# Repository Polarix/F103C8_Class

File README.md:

# STM32F103C8单片机核心板
这是一款设计用于STM32F103C8T6单片机及引脚布局兼容单片机的核心板设计。

原理图和PCB设计使用KiCAD完成，依赖以下符号库和封装库。
 - [kicad_libs_append](https://github.com/Polarix/kicad_libs_append)

## 设计目标
电路设计尝试兼容以下芯片及其引脚兼容型号：

|型号|封装|特征及其改动|
|-|-|-|
|STM32F103C8T6|LQFP-48|以此为基础型号。|
|STM32F030C8T6|LQFP-48|取消一组电源，35、36两个引脚增加PF6、PF7两个GPIO，可复用为USART3的TX、RX两个引脚以及TIM16和TIM17的1通道。|
|STM32F401CCU6|QFN-48|34脚改为VCAP，用作内部电压调节器滤波，并取消了PB11引脚，USART3不可用并被替换为了USART6。|

## 预览图

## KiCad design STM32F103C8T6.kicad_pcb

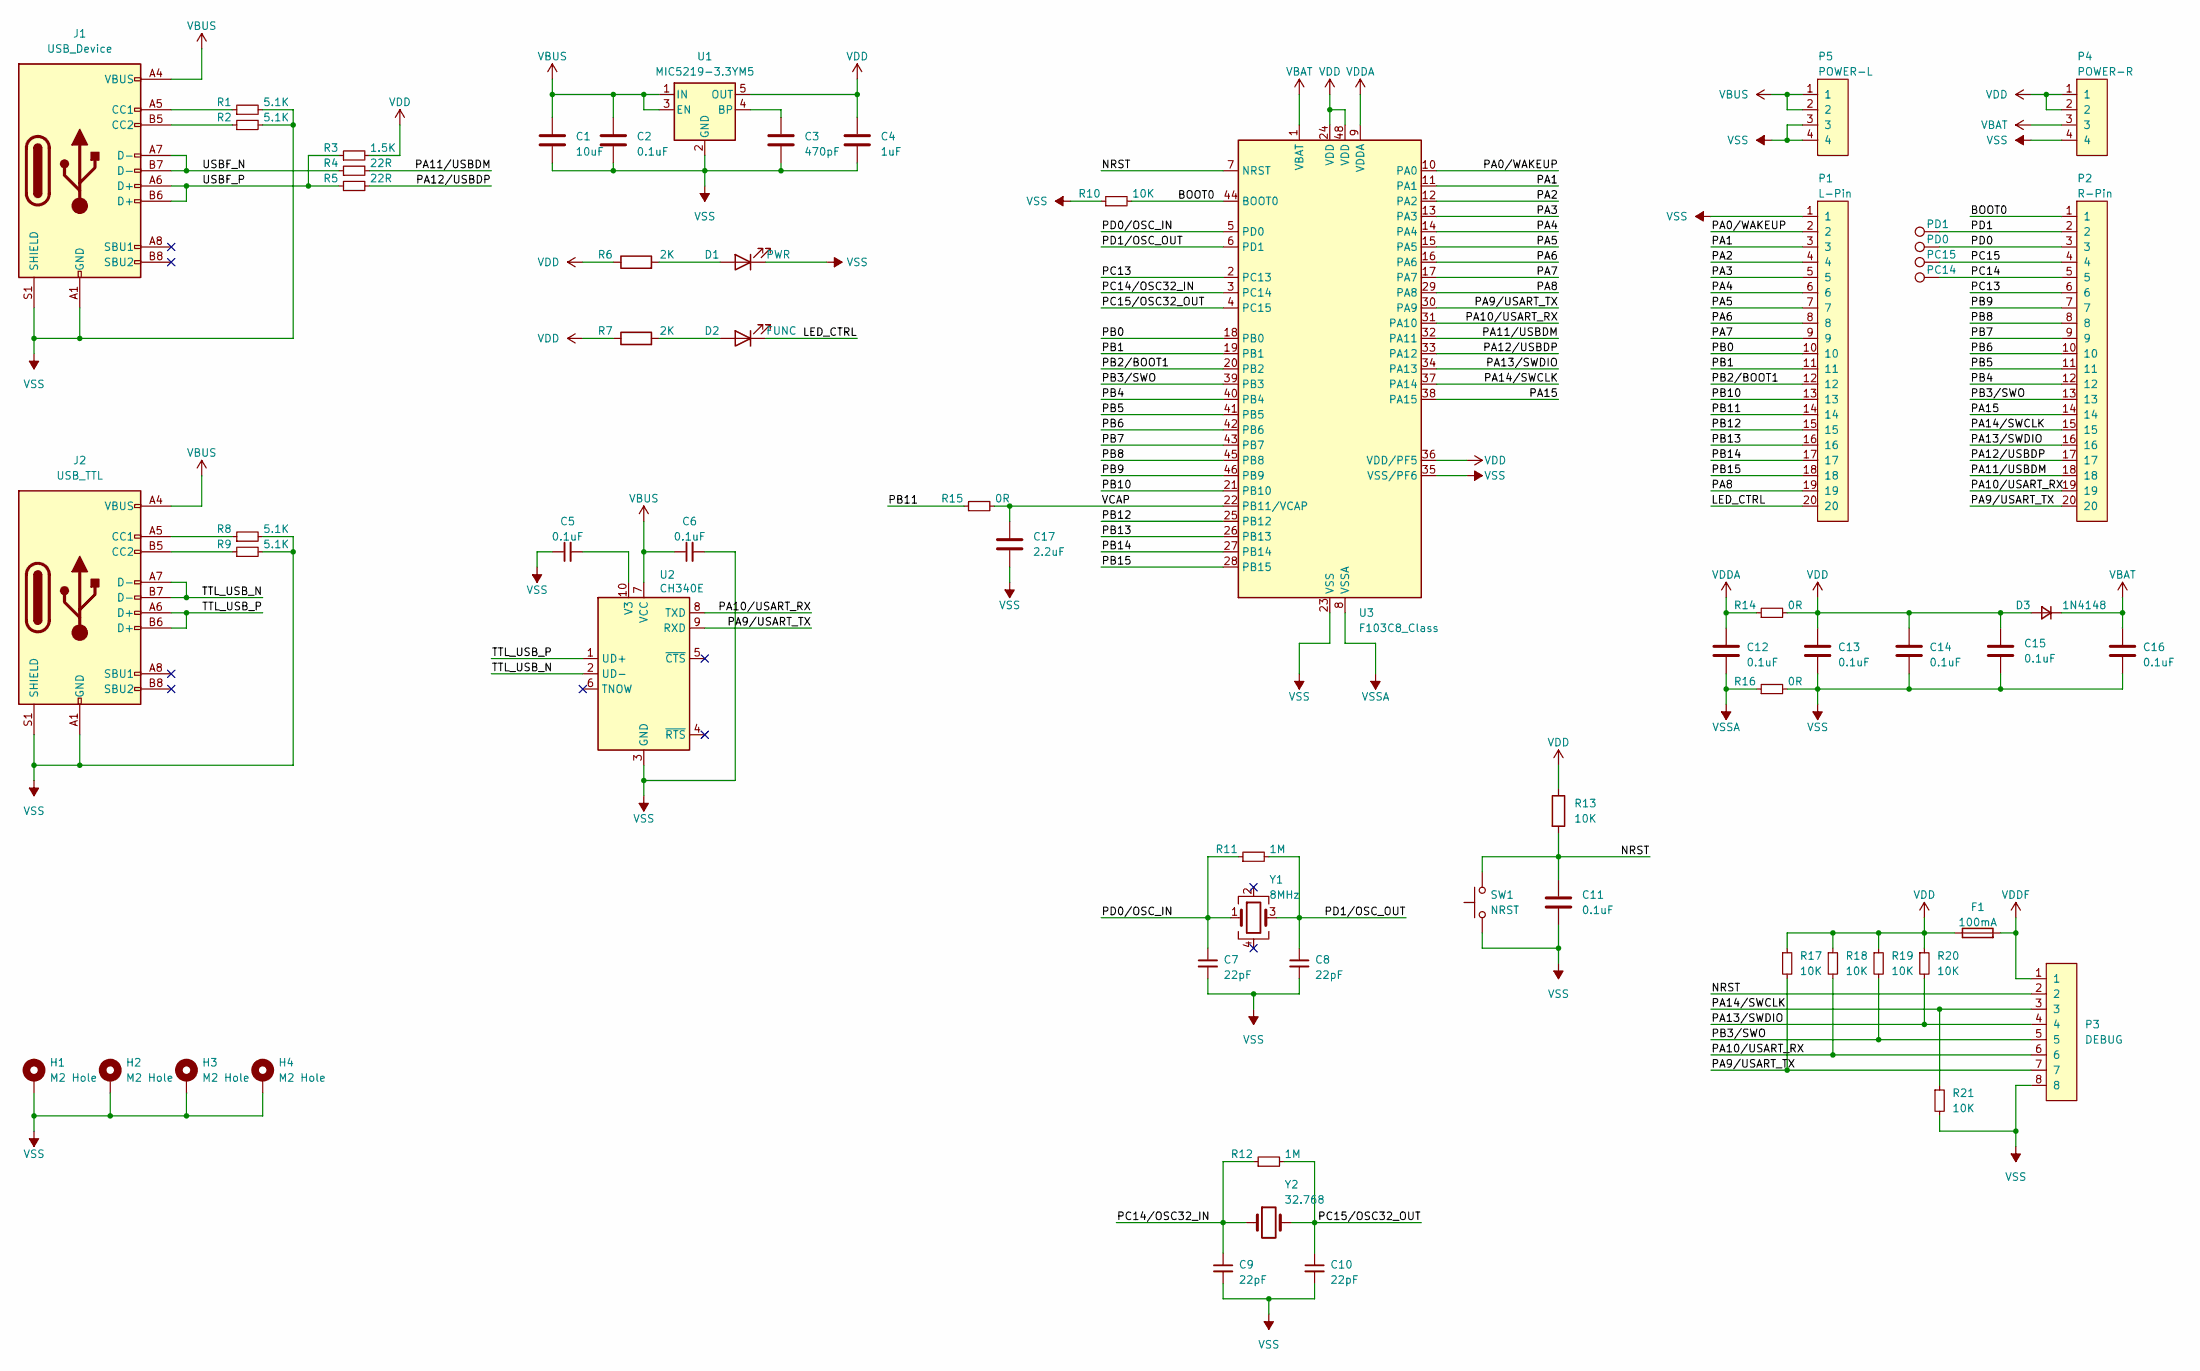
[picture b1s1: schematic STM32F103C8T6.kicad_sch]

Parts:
C1: 10uF; C_0805_2012Metric
C2: 0.1uF; C_0805_2012Metric
C3: 470pF; C_0805_2012Metric
C4: 1uF; C_0805_2012Metric
C5, C6, C11, C12, C13, C14, C15, C16: 0.1uF; C_0603_1608Metric
C7, C8, C9, C10: 22pF; C_0603_1608Metric
C17: 2.2uF; C_0603_1608Metric
D1: PWR; LED_0603_1608Metric
D2: FUNC; LED_0603_1608Metric
D3: 1N4148; D_0603_1608Metric
F1: 100mA; Fuse_0603_1608Metric
H1, H2, H3, H4: M2 Hole; Hole_2×4.5mm
J1: USB_Device; USB_C_Receptacle_HRO_TYPE-C-31-M-12
J2: USB_TTL; USB_C_Receptacle_HRO_TYPE-C-31-M-12
P1: L-Pin; HDR1×20_2.54mm
P2: R-Pin; HDR1×20_2.54mm
P3: DEBUG; JST1.25mm_8P_SMD_Horizontal
P4: POWER-R; HDR1×4_2.54mm
P5: POWER-L; HDR1×4_2.54mm
R1, R2, R8, R9: 5.1K; R_0603_1608Metric
R3: 1.5K; R_0603_1608Metric
R4, R5: 22R; R_0603_1608Metric
R6, R7: 2K; R_0603_1608Metric
R10, R13, R17, R18, R19, R20, R21: 10K; R_0603_1608Metric
R11, R12: 1M; R_0603_1608Metric
R14, R15, R16: 0R; R_0603_1608Metric
SW1: NRST; TS-1070
TP1: PD1; PAD_Semicircular_1mm
TP2: PD0; PAD_Semicircular_1mm
TP3: PC15; PAD_Semicircular_1mm
TP4: PC14; PAD_Semicircular_1mm
U1: MIC5219-3.3YM5; SOT-23-5
U2: CH340E; MSOP-10_3x3mm_P0.5mm
U3: F103C8_Class; LQFP-48_7x7mm_P0.5mm
Y1: 8MHz; Crystal_SMD_3225-4Pin_3.2x2.5mm
Y2: 32.768; Crystal_SMD_3215-2Pin_3.2x1.5mm

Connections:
/BOOT0: P2.1, R10.2, U3.44 (BOOT0)
/LED_CTRL: D2.1 (K), P1.20
/NRST: C11.1, P3.2, R13.2, SW1.2, U3.7 (NRST)
/PA0/WAKEUP: P1.2, U3.10 (PA0)
/PA1: P1.3, U3.11 (PA1)
/PA2: P1.4, U3.12 (PA2)
/PA3: P1.5, U3.13 (PA3)
/PA4: P1.6, U3.14 (PA4)
/PA5: P1.7, U3.15 (PA5)
/PA6: P1.8, U3.16 (PA6)
/PA7: P1.9, U3.17 (PA7)
/PA8: P1.19, U3.29 (PA8)
/PA9/USART_TX: P2.20, P3.7, R17.2, U2.9 (RXD), U3.30 (PA9)
/PA10/USART_RX: P2.19, P3.6, R18.2, U2.8 (TXD), U3.31 (PA10)
/PA11/USBDM: P2.18, R4.2, U3.32 (PA11)
/PA12/USBDP: P2.17, R5.2, U3.33 (PA12)
/PA13/SWDIO: P2.16, P3.4, R20.2, U3.34 (PA13)
/PA14/SWCLK: P2.15, P3.3, R21.1, U3.37 (PA14)
/PA15: P2.14, U3.38 (PA15)
/PB0: P1.10, U3.18 (PB0)
/PB1: P1.11, U3.19 (PB1)
/PB2/BOOT1: P1.12, U3.20 (PB2)
/PB3/SWO: P2.13, P3.5, R19.2, U3.39 (PB3)
/PB4: P2.12, U3.40 (PB4)
/PB5: P2.11, U3.41 (PB5)
/PB6: P2.10, U3.42 (PB6)
/PB7: P2.9, U3.43 (PB7)
/PB8: P2.8, U3.45 (PB8)
/PB9: P2.7, U3.46 (PB9)
/PB10: P1.13, U3.21 (PB10)
/PB11: P1.14, R15.1
/PB12: P1.15, U3.25 (PB12)
/PB13: P1.16, U3.26 (PB13)
/PB14: P1.17, U3.27 (PB14)
/PB15: P1.18, U3.28 (PB15)
/PC13: P2.6, U3.2 (PC13)
/PC14: P2.5, TP4.1
/PC14/OSC32_IN: C9.1, R12.1, U3.3 (PC14), Y2.1
/PC15: P2.4, TP3.1
/PC15/OSC32_OUT: C10.1, R12.2, U3.4 (PC15), Y2.2
/PD0: P2.3, TP2.1
/PD0/OSC_IN: C7.1, R11.1, U3.5 (PD0), Y1.1
/PD1: P2.2, TP1.1
/PD1/OSC_OUT: C8.1, R11.2, U3.6 (PD1), Y1.3
/TTL_USB_N: J2.A7 (D-), J2.B7 (D-), U2.2 (UD-)
/TTL_USB_P: J2.A6 (D+), J2.B6 (D+), U2.1 (UD+)
/USBF_N: J1.A7 (D-), J1.B7 (D-), R4.1
/USBF_P: J1.A6 (D+), J1.B6 (D+), R3.1, R5.1
/VCAP: C17.2, R15.2, U3.22 (PB11/VCAP)
unnamed: D1.2 (A), R6.2
unnamed: D2.2 (A), R7.2
unnamed: J1.A5 (CC1), R1.1
unnamed: J1.B5 (CC2), R2.1
unnamed: J2.A5 (CC1), R8.1
unnamed: J2.B5 (CC2), R9.1
unnamed: C3.1, U1.4 (BP)
unnamed: C5.2, U2.10 (V3)
VBAT: C16.1, D3.1 (K), P4.3, U3.1 (VBAT)
VBUS: C1.1, C2.1, C6.1, J1.A4 (VBUS), J1.A9 (VBUS), J1.B4 (VBUS), J1.B9 (VBUS), J2.A4 (VBUS), J2.A9 (VBUS), J2.B4 (VBUS), J2.B9 (VBUS), P5.1, P5.2, U1.1 (IN), U1.3 (EN), U2.7 (VCC)
VDD: C4.1, C13.1, C14.1, C15.1, D3.2 (A), F1.1, P4.1, P4.2, R3.2, R6.1, R7.1, R13.1, R14.2, R17.1, R18.1, R19.1, R20.1, U1.5 (OUT), U3.24 (VDD), U3.36 (VDD/PF5), U3.48 (VDD)
VDDA: C12.1, R14.1, U3.9 (VDDA)
VDDF: F1.2, P3.1
VSS: C1.2, C2.2, C3.2, C4.2, C5.1, C6.2, C7.2, C8.2, C9.2, C10.2, C11.2, C13.2, C14.2, C15.2, C16.2, C17.1, D1.1 (K), H1.MP, H2.MP, H3.MP, H4.MP, J1.A1 (GND), J1.A12 (GND), J1.B1 (GND), J1.B12 (GND), J1.S1 (SHIELD), J2.A1 (GND), J2.A12 (GND), J2.B1 (GND), J2.B12 (GND), J2.S1 (SHIELD), P1.1, P3.8, P4.4, P5.3, P5.4, R1.2, R2.2, R8.2, R9.2, R10.1, R16.2, R21.2, SW1.1, U1.2 (GND), U2.3 (GND), U3.23 (VSS), U3.35 (VSS/PF6), U3.47 (VSS), U3.49 (VSS)
VSSA: C12.2, R16.1, U3.8 (VSSA)

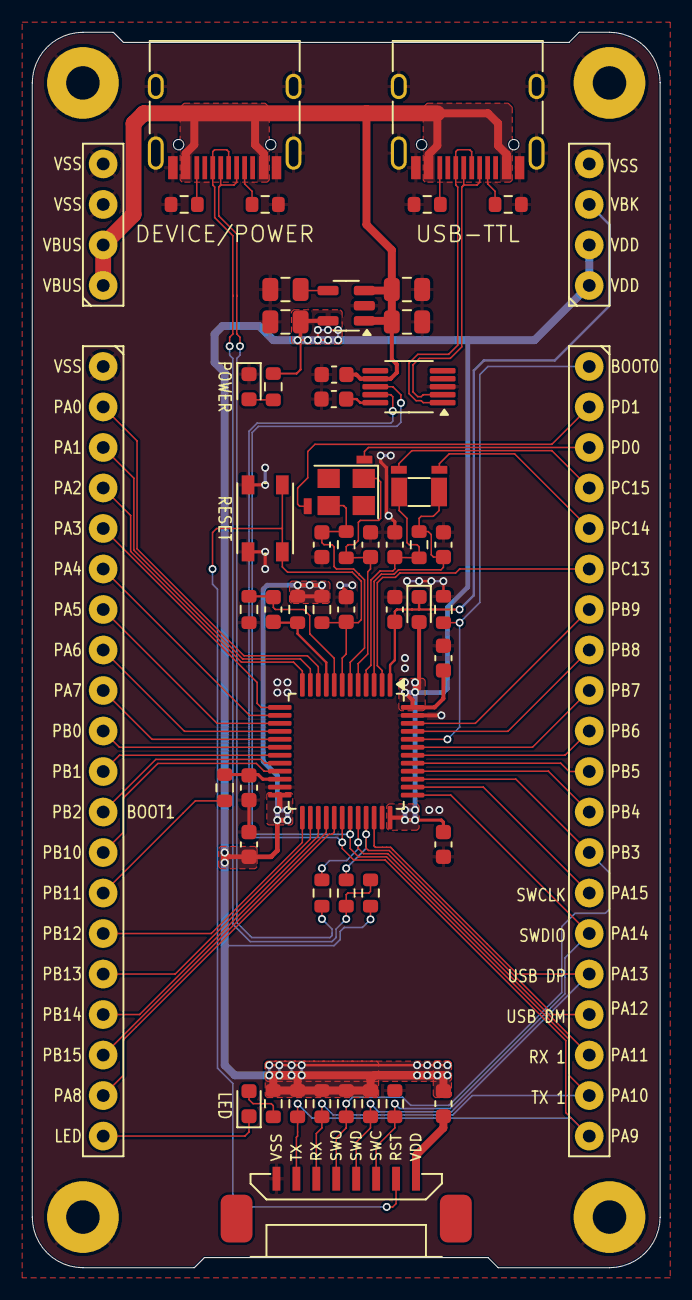
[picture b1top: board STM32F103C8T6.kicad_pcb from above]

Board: 2 copper layers, 39.4 x 77.5 mm, 63 parts (0 on the bottom side), 64 nets.

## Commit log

2025-01-25 增加忽略规则文件
2025-01-25 增加针对自动备份路径的忽略规则
2025-01-25 增加初版KiCAD工程文件
2025-01-25 增肌Readme文件
2025-01-25 增加独立的电源连接端子
2025-01-25 修正晶振匹配电容铺地连接错误的问题
2025-01-25 更新自述文件
2025-01-25 修正电器规则和布线错误
2025-01-25 更新电路设计，兼容F401CC芯片
2025-01-25 更新描述文件
2025-01-25 优化电源走线
2025-01-25 更新说明文件，增加3D预览图
2025-01-25 更新Git忽略文件规则
2025-01-25 更新引脚链接，增加晶振引脚的跳接焊盘
2025-02-03 修改调试器接口的电源走线
2025-02-05 修正了调试器接口的电源线宽度，底面增加了可以标注型号的留白
